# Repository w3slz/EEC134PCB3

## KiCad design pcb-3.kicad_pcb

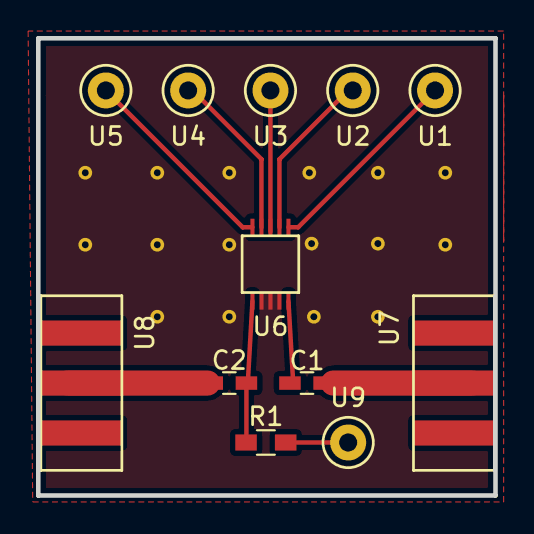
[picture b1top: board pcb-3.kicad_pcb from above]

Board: 2 copper layers, 25.4 x 25.4 mm, 12 parts (0 on the bottom side), 11 nets.

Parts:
C1, C2: 47p; C_0603_HandSoldering
R1: 10k; R_0603_HandSoldering
U1: V1; Test_Point_Keystone_5000-5004_Miniature
U2: V2; Test_Point_Keystone_5000-5004_Miniature
U3: V3; Test_Point_Keystone_5000-5004_Miniature
U4: V4; Test_Point_Keystone_5000-5004_Miniature
U5: V5; Test_Point_Keystone_5000-5004_Miniature
U6: SKY12322-86LF
U7: J1; SMA
U8: J2; SMA
U9: VS; Test_Point_Keystone_5000-5004_Miniature

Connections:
GND: U6.7, U6.8, U6.9
unnamed: C1.1, U6.10
unnamed: C1.2, U7.2
unnamed: C2.1, R1.1, U6.6
unnamed: C2.2, U8.2
unnamed: R1.2, U9.1
unnamed: U1.1, U6.1
unnamed: U2.1, U6.2
unnamed: U3.1, U6.3
unnamed: U4.1, U6.4
unnamed: U5.1, U6.5
